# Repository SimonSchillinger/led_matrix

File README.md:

# led_matrix
Code for my private RaspberryPi Project

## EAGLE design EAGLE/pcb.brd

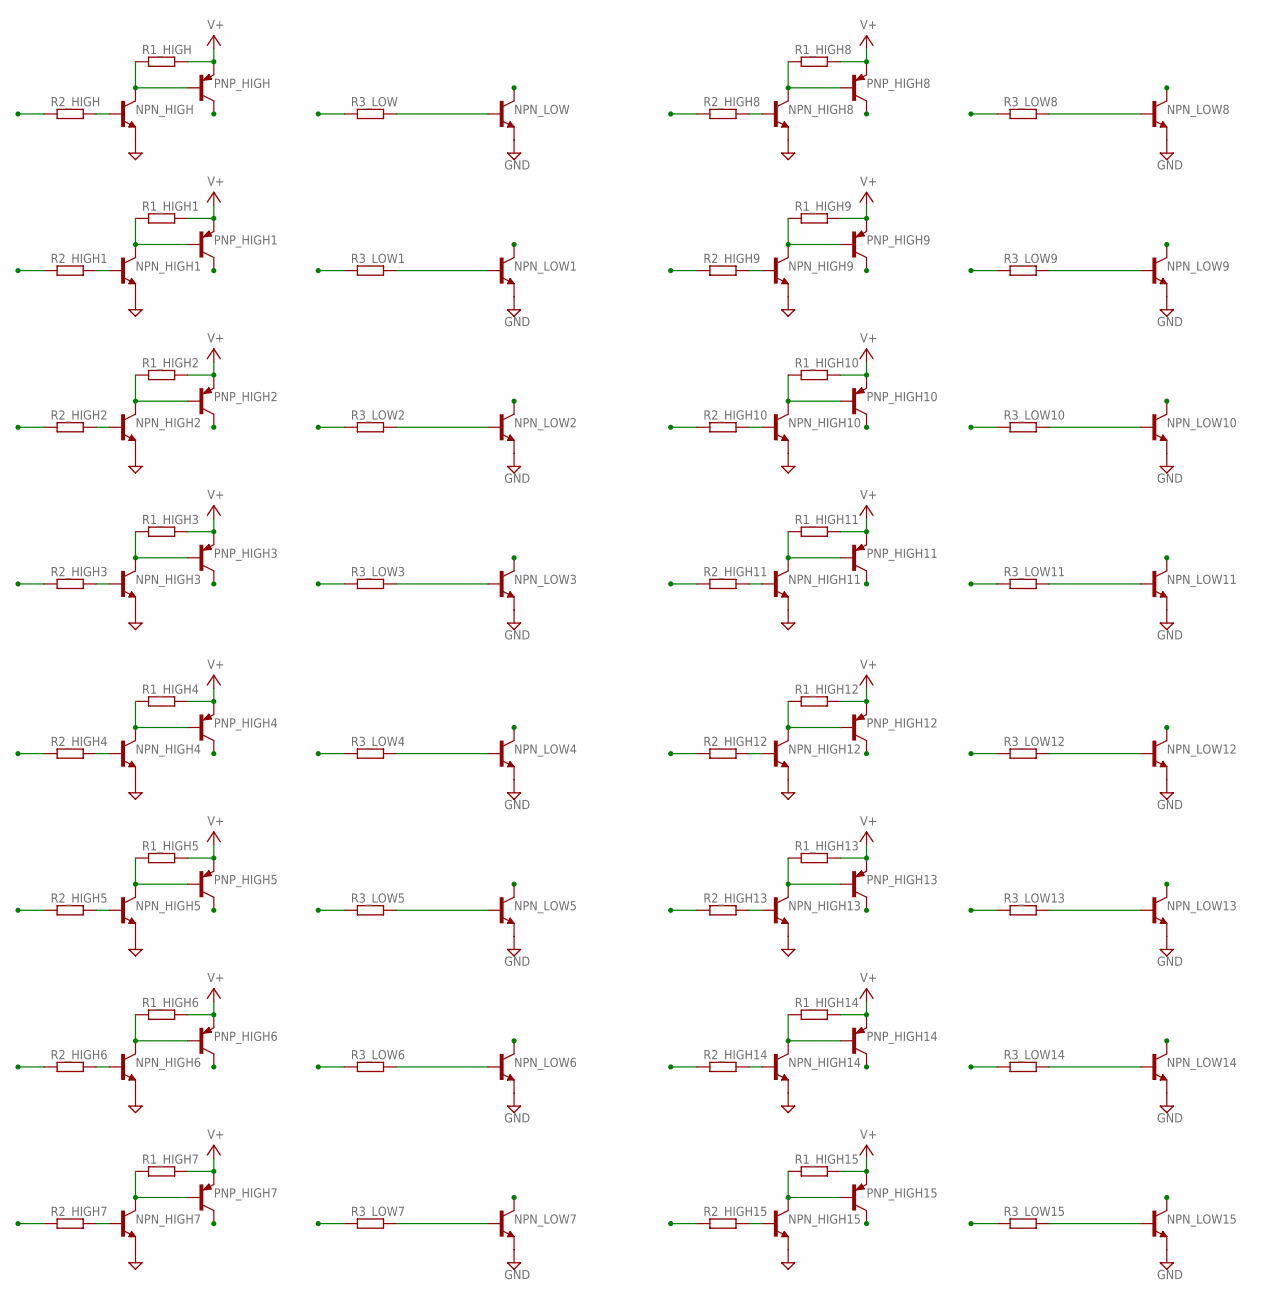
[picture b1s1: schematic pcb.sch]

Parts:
NPN_HIGH, NPN_HIGH1, NPN_HIGH2, NPN_HIGH3, NPN_HIGH4, NPN_HIGH5, NPN_HIGH6, NPN_HIGH7, NPN_HIGH8, NPN_HIGH9, NPN_HIGH10, NPN_HIGH11, NPN_HIGH12, NPN_HIGH13, NPN_HIGH14, NPN_HIGH15: -NPN-TO92-ECB; TO92-ECB
NPN_LOW, NPN_LOW1, NPN_LOW2, NPN_LOW3, NPN_LOW4, NPN_LOW5, NPN_LOW6, NPN_LOW7, NPN_LOW8, NPN_LOW9, NPN_LOW10, NPN_LOW11, NPN_LOW12, NPN_LOW13, NPN_LOW14, NPN_LOW15: -NPN-TO92-ECB; TO92-ECB
PNP_HIGH, PNP_HIGH1, PNP_HIGH2, PNP_HIGH3, PNP_HIGH4, PNP_HIGH5, PNP_HIGH6, PNP_HIGH7, PNP_HIGH8, PNP_HIGH9, PNP_HIGH10, PNP_HIGH11, PNP_HIGH12, PNP_HIGH13, PNP_HIGH14, PNP_HIGH15: -PNP-TO92-BEC; TO92-BEC
R1_HIGH, R1_HIGH1, R1_HIGH2, R1_HIGH3, R1_HIGH4, R1_HIGH5, R1_HIGH6, R1_HIGH7, R1_HIGH8, R1_HIGH9, R1_HIGH10, R1_HIGH11, R1_HIGH12, R1_HIGH13, R1_HIGH14, R1_HIGH15, R2_HIGH, R2_HIGH1, R2_HIGH2, R2_HIGH3, R2_HIGH4, R2_HIGH5, R2_HIGH6, R2_HIGH7, R2_HIGH8, R2_HIGH9, R2_HIGH10, R2_HIGH11, R2_HIGH12, R2_HIGH13, R2_HIGH14, R2_HIGH15, R3_LOW, R3_LOW1, R3_LOW2, R3_LOW3, R3_LOW4, R3_LOW5, R3_LOW6, R3_LOW7, R3_LOW8, R3_LOW9, R3_LOW10, R3_LOW11, R3_LOW12, R3_LOW13, R3_LOW14, R3_LOW15: R-EU_0613/15; P0613/15

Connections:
GND: NPN_HIGH.E, NPN_HIGH1.E, NPN_HIGH2.E, NPN_HIGH3.E, NPN_HIGH4.E, NPN_HIGH5.E, NPN_HIGH6.E, NPN_HIGH7.E, NPN_HIGH8.E, NPN_HIGH9.E, NPN_HIGH10.E, NPN_HIGH11.E, NPN_HIGH12.E, NPN_HIGH13.E, NPN_HIGH14.E, NPN_HIGH15.E, NPN_LOW.E, NPN_LOW1.E, NPN_LOW2.E, NPN_LOW3.E, NPN_LOW4.E, NPN_LOW5.E, NPN_LOW6.E, NPN_LOW7.E, NPN_LOW8.E, NPN_LOW9.E, NPN_LOW10.E, NPN_LOW11.E, NPN_LOW12.E, NPN_LOW13.E, NPN_LOW14.E, NPN_LOW15.E
unnamed: NPN_HIGH.B, R2_HIGH.2
unnamed: NPN_HIGH.C, PNP_HIGH.B, R1_HIGH.1
unnamed: NPN_LOW.B, R3_LOW.2
unnamed: NPN_HIGH1.B, R2_HIGH1.2
unnamed: NPN_HIGH1.C, PNP_HIGH1.B, R1_HIGH1.1
unnamed: NPN_LOW1.B, R3_LOW1.2
unnamed: NPN_HIGH2.B, R2_HIGH2.2
unnamed: NPN_HIGH2.C, PNP_HIGH2.B, R1_HIGH2.1
unnamed: NPN_LOW2.B, R3_LOW2.2
unnamed: NPN_HIGH3.B, R2_HIGH3.2
unnamed: NPN_HIGH3.C, PNP_HIGH3.B, R1_HIGH3.1
unnamed: NPN_LOW3.B, R3_LOW3.2
unnamed: NPN_HIGH4.B, R2_HIGH4.2
unnamed: NPN_HIGH4.C, PNP_HIGH4.B, R1_HIGH4.1
unnamed: NPN_LOW4.B, R3_LOW4.2
unnamed: NPN_HIGH5.B, R2_HIGH5.2
unnamed: NPN_HIGH5.C, PNP_HIGH5.B, R1_HIGH5.1
unnamed: NPN_LOW5.B, R3_LOW5.2
unnamed: NPN_HIGH6.B, R2_HIGH6.2
unnamed: NPN_HIGH6.C, PNP_HIGH6.B, R1_HIGH6.1
unnamed: NPN_LOW6.B, R3_LOW6.2
unnamed: NPN_HIGH7.B, R2_HIGH7.2
unnamed: NPN_HIGH7.C, PNP_HIGH7.B, R1_HIGH7.1
unnamed: NPN_LOW7.B, R3_LOW7.2
unnamed: NPN_HIGH8.B, R2_HIGH8.2
unnamed: NPN_HIGH8.C, PNP_HIGH8.B, R1_HIGH8.1
unnamed: NPN_LOW8.B, R3_LOW8.2
unnamed: NPN_HIGH9.B, R2_HIGH9.2
unnamed: NPN_HIGH9.C, PNP_HIGH9.B, R1_HIGH9.1
unnamed: NPN_LOW9.B, R3_LOW9.2
unnamed: NPN_HIGH10.B, R2_HIGH10.2
unnamed: NPN_HIGH10.C, PNP_HIGH10.B, R1_HIGH10.1
unnamed: NPN_LOW10.B, R3_LOW10.2
unnamed: NPN_HIGH11.B, R2_HIGH11.2
unnamed: NPN_HIGH11.C, PNP_HIGH11.B, R1_HIGH11.1
unnamed: NPN_LOW11.B, R3_LOW11.2
unnamed: NPN_HIGH12.B, R2_HIGH12.2
unnamed: NPN_HIGH12.C, PNP_HIGH12.B, R1_HIGH12.1
unnamed: NPN_LOW12.B, R3_LOW12.2
unnamed: NPN_HIGH13.B, R2_HIGH13.2
unnamed: NPN_HIGH13.C, PNP_HIGH13.B, R1_HIGH13.1
unnamed: NPN_LOW13.B, R3_LOW13.2
unnamed: NPN_HIGH14.B, R2_HIGH14.2
unnamed: NPN_HIGH14.C, PNP_HIGH14.B, R1_HIGH14.1
unnamed: NPN_LOW14.B, R3_LOW14.2
unnamed: NPN_HIGH15.B, R2_HIGH15.2
unnamed: NPN_HIGH15.C, PNP_HIGH15.B, R1_HIGH15.1
unnamed: NPN_LOW15.B, R3_LOW15.2
V+: PNP_HIGH.E, PNP_HIGH1.E, PNP_HIGH2.E, PNP_HIGH3.E, PNP_HIGH4.E, PNP_HIGH5.E, PNP_HIGH6.E, PNP_HIGH7.E, PNP_HIGH8.E, PNP_HIGH9.E, PNP_HIGH10.E, PNP_HIGH11.E, PNP_HIGH12.E, PNP_HIGH13.E, PNP_HIGH14.E, PNP_HIGH15.E, R1_HIGH.2, R1_HIGH1.2, R1_HIGH2.2, R1_HIGH3.2, R1_HIGH4.2, R1_HIGH5.2, R1_HIGH6.2, R1_HIGH7.2, R1_HIGH8.2, R1_HIGH9.2, R1_HIGH10.2, R1_HIGH11.2, R1_HIGH12.2, R1_HIGH13.2, R1_HIGH14.2, R1_HIGH15.2

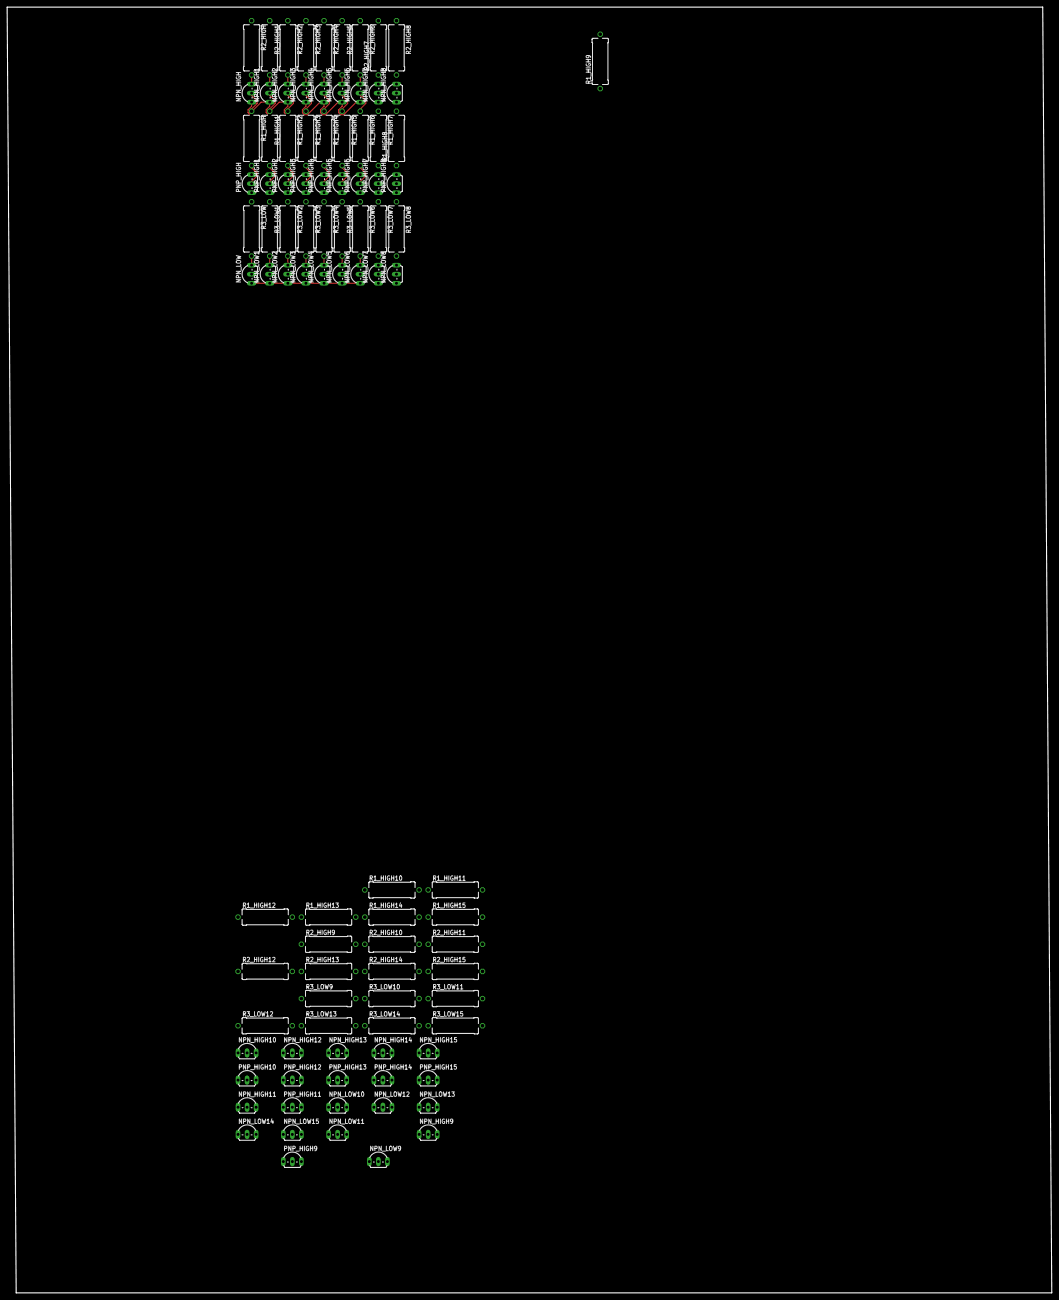
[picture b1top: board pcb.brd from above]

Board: 2 copper layers, 293.0 x 360.7 mm, 96 parts (0 on the bottom side), 50 nets.

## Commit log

2021-01-28 final commit for now
2021-01-28 Schaltplan image added
